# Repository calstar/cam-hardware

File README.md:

View this project on [CADLAB.io](https://cadlab.io/project/22831). 

# STAR - CAS: Common Avionics Stack

Contents
* **core** - base module with microcontroller and a few sensors
* **radio** - comms module based on RFM69HCW radio

## Submodules and symlinks
* In order to allow KiCad to correctly reference hierarchical blocks, every module's subdirectory needs a hardware-sch-blocks subdirectory. However, this leads to a LOT of redundant submodules. Instead, hardware-sch-blocks is submoduled at the top level, and each module subdirectory contains a symlink back up to that submodule. If you need to create a symlink for a new module, use the ln -fs command.

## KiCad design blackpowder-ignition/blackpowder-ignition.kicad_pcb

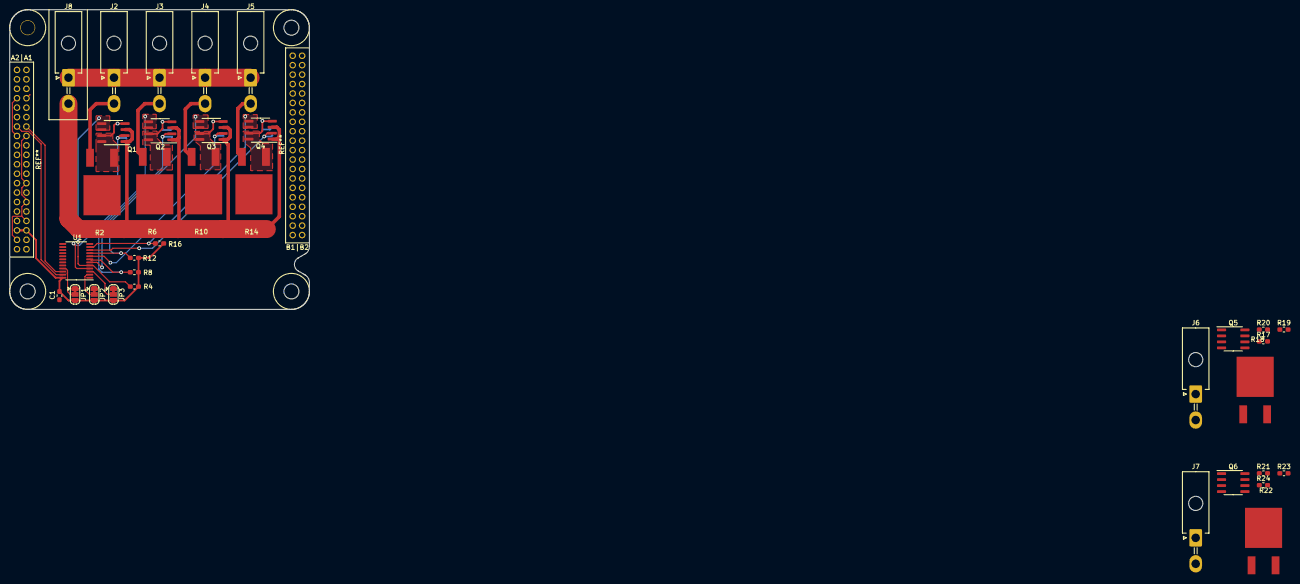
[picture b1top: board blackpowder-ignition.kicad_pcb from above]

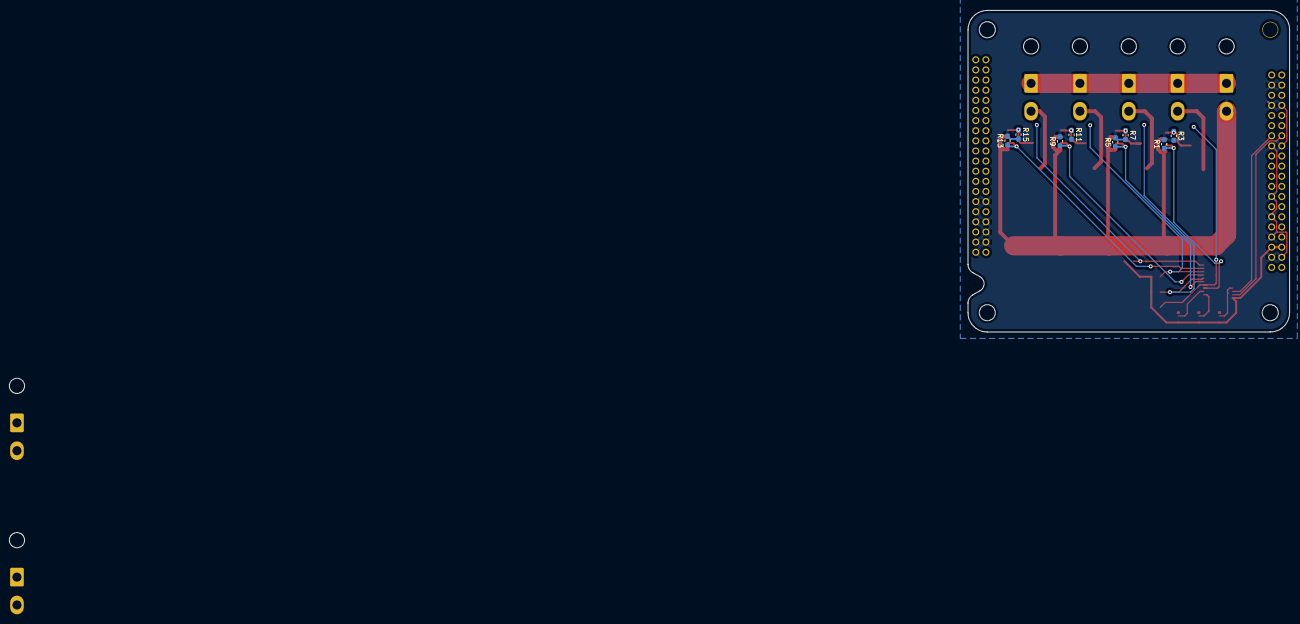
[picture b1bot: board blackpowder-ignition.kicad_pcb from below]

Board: 2 copper layers, 63.5 x 63.5 mm, 43 parts (8 on the bottom side), 33 nets.

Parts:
C1: 100nF; C_0603_1608Metric_Pad1.05x0.95mm_HandSolder
J1: CAS_stacking; CAS_physical
J2, J3, J4, J5, J6, J7, J8: Conn_01x02; Molex_Mini-Fit_Jr_5569-02A2_2x01_P4.20mm_Horizontal
JP1, JP2, JP3: SolderJumper_3_Bridged12; SolderJumper-3_P1.3mm_Bridged12_RoundedPad1.0x1.5mm
Q1, Q2, Q3, Q4, Q5, Q6: FDS6898A; SOIC-8_3.9x4.9mm_P1.27mm
R1, R3, R4, R5, R7, R8, R9, R11, R12, R13, R15, R16, R17, R19, R20, R21, R23, R24: R; R_0603_1608Metric_Pad1.05x0.95mm_HandSolder
R2, R6, R10, R14, R18, R22: R; PWR163
U1: TCA9555PWR; TSSOP-24_4.4x7.8mm_P0.65mm

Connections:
+3V3: C1.1, J1.A35, J1.A36, JP1.3, JP2.3, JP3.3, R4.1, R8.1, R12.1, R16.1, R20.1, R24.1, U1.24
+5V: J1.A5, J1.A6
+BATT: J1.A39, J1.A40, J2.1, J3.1, J4.1, J5.1, J6.1, J7.1, J8.1
/A0: JP1.2, U1.21
/A1: JP2.2, U1.2
/A2: JP3.2, U1.3
/CAS_bus/I2C0_SCL: J1.A13, U1.22
/CAS_bus/I2C0_SDA: J1.A14, U1.23
/igniteA: Q1.2, R1.1, U1.4
/igniteB: Q2.2, R5.1, U1.6
/igniteC: Q3.2, R9.1, U1.8
/igniteD: Q4.2, R13.1, U1.10
/igniteE: Q5.2, R17.1, U1.13
/igniteF: Q6.2, R21.1, U1.15
/~contA~: Q1.5, Q1.6, R4.2, U1.5
/~contB~: Q2.5, Q2.6, R8.2, U1.7
/~contC~: Q3.5, Q3.6, R12.2, U1.9
/~contD~: Q4.5, Q4.6, R16.2, U1.11
/~contE~: Q5.5, Q5.6, R20.2, U1.14
/~igniteF~: Q6.5, Q6.6, R24.2, U1.16
GND: C1.2, J1.A3, J1.A4, J1.A7, J1.A8, J1.A15, J1.A16, J1.A25, J1.A29, J1.A33, J1.A37, J1.A38, J1.B2, J1.B3, J1.B4, J1.B5, J1.B7, J1.B8, J1.B10, J1.B11, J1.B12, J8.2, JP1.1, JP2.1, JP3.1, Q1.1, Q1.3, Q2.1, Q2.3, Q3.1, Q3.3, Q4.1, Q4.3, Q5.1, Q5.3, Q6.1, Q6.3, R1.2, R3.2, R5.2, R7.2, R9.2, R11.2, R13.2, R15.2, R17.2, R19.2, R21.2, R23.2, U1.12
unnamed: J2.2, R2.1
unnamed: J3.2, R6.1
unnamed: J4.2, R10.1
unnamed: J5.2, R14.1
unnamed: J6.2, R18.1
unnamed: J7.2, R22.1
unnamed: Q1.4, Q1.7, Q1.8, R2.2, R3.1
unnamed: Q2.4, Q2.7, Q2.8, R6.2, R7.1
unnamed: Q3.4, Q3.7, Q3.8, R10.2, R11.1
unnamed: Q4.4, Q4.7, Q4.8, R14.2, R15.1
unnamed: Q5.4, Q5.7, Q5.8, R18.2, R19.1
unnamed: Q6.4, Q6.7, Q6.8, R22.2, R23.1

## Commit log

2020-02-23 radio proj init
2020-03-01 I2C-SPI bridge
2020-03-01 Core CAM
2020-03-01 pushing end-of-workday changes to radio module
2020-03-07 add CAM interconnects
2020-03-07 Updated core with IMU and altimiter as specified on pinout
2020-03-08 Updated core with IMU hierarchical block
2020-03-08 Updated core with altimeter hierarchical block
2020-03-08 added connector to core and determined pinout
2020-03-08 update connector pinout on radio
2020-03-21 schematic of ignition module. only ignition circuit, no bus connections
2020-04-24 new symbols for stacking
2020-04-26 Backlink to CADLAB.io has been added.
2020-04-29 move CAS stacking connectors to common lib
2020-04-29 bump hardware-sch-blocks pre-PR
2020-04-29 bump hardware-sch-blocks
2020-04-29 Fix Aled's comments on PR #1
2020-04-29 rollback cache nuke in #1
2020-04-29 Used symlinks to eliminate redundant submodules
2020-04-29 Update README.md
    renamed CAM to CAS
2020-04-29 Add CAS bus sheet to core
2020-05-01 SPI/I2C boilerplate
2020-05-01 blackpowder new design
2020-05-01 made hierarchical block for individual ignition circuit
2020-05-19 Update README to describe submodule symlinking
2020-05-30 symlink to hardware sch blocks
2020-05-30 added hierarchical sch sheet for bus, address jummper pads, connections from io expander to subcircuits
2020-05-31 added power connector
2020-05-31 trying to push radio again
2020-05-31 Core schematic complete, review needed
2020-06-14 initial layout
2020-06-15 fixed da stuff
2020-06-21 nicer models, finished routing
2020-06-22 Fixed some schematic issues
2020-06-22 Amended BATT+
2020-06-23 Fixed SD card reader connection
2020-06-27 hopefully fix submodules
2020-06-28 Done schematic
2020-08-10 Finished schematics except for MCU pinout
2020-08-26 Update core schematics
2020-09-13 Prepare PR
2020-10-05 Sync changes
